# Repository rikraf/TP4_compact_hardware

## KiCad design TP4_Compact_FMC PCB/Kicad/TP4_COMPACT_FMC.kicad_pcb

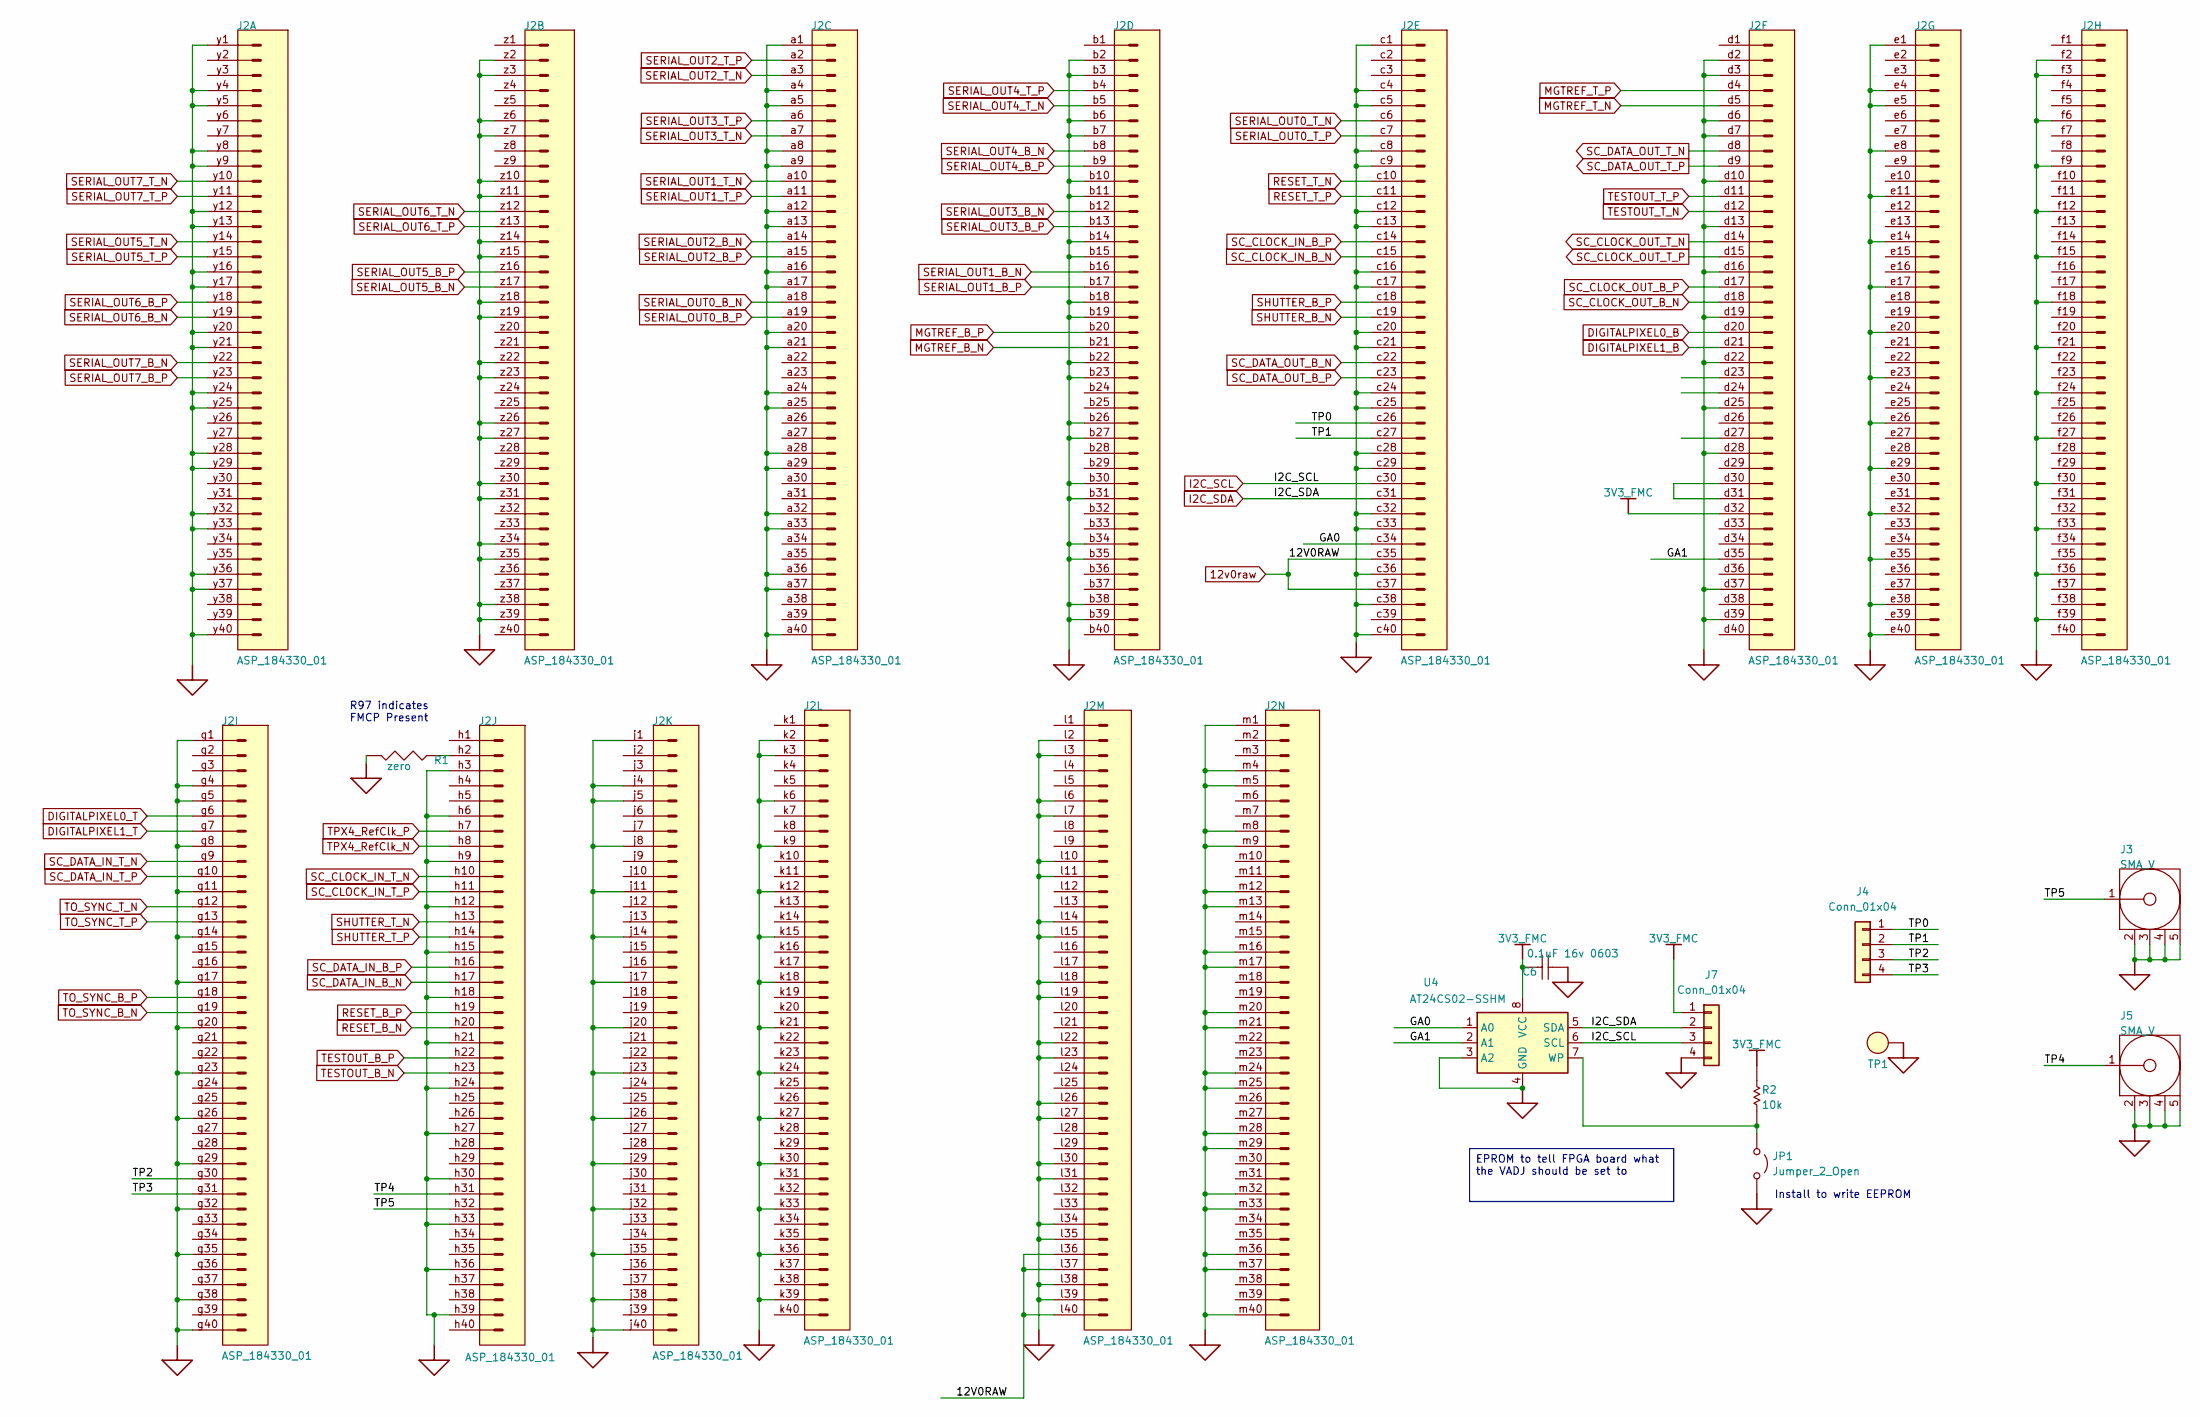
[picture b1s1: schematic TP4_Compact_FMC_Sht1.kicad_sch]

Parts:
C6: 0.1uF 0603; C_0603_1608Metric; MANUFACTURER_PART_NUMBER C0603C104K4RACTU
J2: ASP_184330_01; SAMTEC_ASP_184330_01; MANUFACTURER_PART_NUMBER ASP-184330-01
J3, J5: SMA_V; SMA_Amphenol_901-144_Vertical; MANUFACTURER_PART_NUMBER SMA-J-P-H-ST-MT1
J4, J7: Conn_01x04; PinHeader_1x04_P2.54mm_Vertical; MANUFACTURER_PART_NUMBER 61300411121
JP1: Jumper_2_Open; TestPoint_2Pads_Pitch2.54mm_Drill0.8mm; MANUFACTURER_PART_NUMBER 61300211121
R1: zero; R_0603_1608Metric; MANUFACTURER_PART_NUMBER RC0603JR-070RL
R2: 10k; R_0603_1608Metric; MANUFACTURER_PART_NUMBER CR0603-FX-1002ELF
TP1: through-hole pad; SolderWire-0.1sqmm_1x01_D0.4mm_OD1mm
U4: AT24CS02-SSHM; SOIC-8_3.9x4.9mm_P1.27mm; MANUFACTURER_PART_NUMBER AT24C02C-SSHM-T

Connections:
3V3_FMC: C6.2, J2.d32, J7.1, R2.2, U4.8 (VCC)
12v0raw: J2.c35, J2.c37, J2.l36, J2.l37, J2.l40; also elsewhere on the board
/FMC_osc/GA0: J2.c34, U4.1 (A0)
/FMC_osc/GA1: J2.d35, U4.2 (A1)
/FMC_osc/TP0: J2.c26, J4.1
/FMC_osc/TP1: J2.c27, J4.2
/FMC_osc/TP2: J2.g30, J4.3
/FMC_osc/TP3: J2.g31, J4.4
/FMC_osc/TP4: J2.h31, J5.1 (Signal)
/FMC_osc/TP5: J2.h32, J3.1 (Signal)
DIGITALPIXEL0_B: J2.d20; also elsewhere on the board
DIGITALPIXEL0_T: J2.g6; also elsewhere on the board
DIGITALPIXEL1_B: J2.d21; also elsewhere on the board
DIGITALPIXEL1_T: J2.g7; also elsewhere on the board
GND: C6.1, J2.a1, J2.a4, J2.a5, J2.a8, J2.a9, J2.a12, J2.a13, J2.a16, J2.a17, J2.a20, J2.a21, J2.a24, J2.a25, J2.a28, J2.a29, J2.a32, J2.a33, J2.a36, J2.a37, J2.a40, J2.b2, J2.b3, J2.b6, J2.b7, J2.b10, J2.b11, J2.b14, J2.b15, J2.b18, J2.b19, J2.b22, J2.b23, J2.b26, J2.b27, J2.b30, J2.b31, J2.b34, J2.b35, J2.b38, J2.b39, J2.c1, J2.c4, J2.c5, J2.c8, J2.c9, J2.c12, J2.c13, J2.c16, J2.c17, J2.c20, J2.c21, J2.c24, J2.c25, J2.c28, J2.c29, J2.c32, J2.c33, J2.c36, J2.c38, J2.c40, J2.d2, J2.d3, J2.d6, J2.d7, J2.d10, J2.d13, J2.d16, J2.d19, J2.d22, J2.d25, J2.d28, J2.d37, J2.d39, J2.e1, J2.e4, J2.e5, J2.e8, J2.e11, J2.e14, J2.e17, J2.e20, J2.e23, J2.e26, J2.e29, J2.e32, J2.e35, J2.e38, J2.e40, J2.f2, J2.f3, J2.f6, J2.f9, J2.f12, J2.f15, J2.f18, J2.f21, J2.f24, J2.f27, J2.f30, J2.f33, J2.f36, J2.f39, J2.g1, J2.g4, J2.g5, J2.g8, J2.g11, J2.g14, J2.g17, J2.g20, J2.g23, J2.g26, J2.g29, J2.g32, J2.g35, J2.g38, J2.g40, J2.h3, J2.h6, J2.h9, J2.h12, J2.h15, J2.h18, J2.h21, J2.h24, J2.h27, J2.h30, J2.h33, J2.h36, J2.h39, J2.j1, J2.j4, J2.j5, J2.j8, J2.j11, J2.j14, J2.j17, J2.j20, J2.j23, J2.j26, J2.j29, J2.j32, J2.j35, J2.j38, J2.j40, J2.k2, J2.k3, J2.k6, J2.k9, J2.k12, J2.k15, J2.k18, J2.k21, J2.k24, J2.k27, J2.k30, J2.k33, J2.k36, J2.k39, J2.l2, J2.l3, J2.l6, J2.l7, J2.l10, J2.l11, J2.l14, J2.l15, J2.l18, J2.l19, J2.l22, J2.l23, J2.l26, J2.l27, J2.l30, J2.l31, J2.l34, J2.l35, J2.l38, J2.l39, J2.m1, J2.m4, J2.m5, J2.m8, J2.m9, J2.m12, J2.m13, J2.m16, J2.m17, J2.m20, J2.m21, J2.m24, J2.m25, J2.m28, J2.m29, J2.m32, J2.m33, J2.m36, J2.m37, J2.m40, J2.y1, J2.y4, J2.y5, J2.y8, J2.y9, J2.y12, J2.y13, J2.y16, J2.y17, J2.y20, J2.y21, J2.y24, J2.y25, J2.y28, J2.y29, J2.y32, J2.y33, J2.y36, J2.y37, J2.y40, J2.z2, J2.z3, J2.z6, J2.z7, J2.z10, J2.z11, J2.z14, J2.z15, J2.z18, J2.z19, J2.z22, J2.z23, J2.z26, J2.z27, J2.z30, J2.z31, J2.z34, J2.z35, J2.z38, J2.z39, J3.2 (GND), J3.3 (GND), J3.4 (GND), J3.5 (GND), J5.2 (GND), J5.3 (GND), J5.4 (GND), J5.5 (GND), J7.4, JP1.2 (B), R1.2, TP1.1, U4.3 (A2), U4.4 (GND); also elsewhere on the board
I2C_SCL: J2.c30, J7.3, U4.6 (SCL); also elsewhere on the board
I2C_SDA: J2.c31, J7.2, U4.5 (SDA); also elsewhere on the board
MGTREF_B_N: J2.b21; also elsewhere on the board
MGTREF_B_P: J2.b20; also elsewhere on the board
MGTREF_T_N: J2.d5; also elsewhere on the board
MGTREF_T_P: J2.d4; also elsewhere on the board
unnamed: J2.d30, J2.d31
unnamed: J2.h2, R1.1
unnamed: JP1.1 (A), R2.1, U4.7 (WP)
RESET_B_N: J2.h20; also elsewhere on the board
RESET_B_P: J2.h19; also elsewhere on the board
RESET_T_N: J2.c10; also elsewhere on the board
RESET_T_P: J2.c11; also elsewhere on the board
SC_CLOCK_IN_B_N: J2.c15; also elsewhere on the board
SC_CLOCK_IN_B_P: J2.c14; also elsewhere on the board
SC_CLOCK_IN_T_N: J2.h10; also elsewhere on the board
SC_CLOCK_IN_T_P: J2.h11; also elsewhere on the board
SC_CLOCK_OUT_B_N: J2.d18; also elsewhere on the board
SC_CLOCK_OUT_B_P: J2.d17; also elsewhere on the board
SC_CLOCK_OUT_T_N: J2.d14; also elsewhere on the board
SC_CLOCK_OUT_T_P: J2.d15; also elsewhere on the board
SC_DATA_IN_B_N: J2.h17; also elsewhere on the board
SC_DATA_IN_B_P: J2.h16; also elsewhere on the board
SC_DATA_IN_T_N: J2.g9; also elsewhere on the board
SC_DATA_IN_T_P: J2.g10; also elsewhere on the board
SC_DATA_OUT_B_N: J2.c22; also elsewhere on the board
SC_DATA_OUT_B_P: J2.c23; also elsewhere on the board
SC_DATA_OUT_T_N: J2.d8; also elsewhere on the board
SC_DATA_OUT_T_P: J2.d9; also elsewhere on the board
SERIAL_OUT0_B_N: J2.a18; also elsewhere on the board
SERIAL_OUT0_B_P: J2.a19; also elsewhere on the board
SERIAL_OUT0_T_N: J2.c6; also elsewhere on the board
SERIAL_OUT0_T_P: J2.c7; also elsewhere on the board
SERIAL_OUT1_B_N: J2.b16; also elsewhere on the board
SERIAL_OUT1_B_P: J2.b17; also elsewhere on the board
SERIAL_OUT1_T_N: J2.a10; also elsewhere on the board
SERIAL_OUT1_T_P: J2.a11; also elsewhere on the board
SERIAL_OUT2_B_N: J2.a14; also elsewhere on the board
SERIAL_OUT2_B_P: J2.a15; also elsewhere on the board
SERIAL_OUT2_T_N: J2.a3; also elsewhere on the board
SERIAL_OUT2_T_P: J2.a2; also elsewhere on the board
SERIAL_OUT3_B_N: J2.b12; also elsewhere on the board
SERIAL_OUT3_B_P: J2.b13; also elsewhere on the board
SERIAL_OUT3_T_N: J2.a7; also elsewhere on the board
SERIAL_OUT3_T_P: J2.a6; also elsewhere on the board
SERIAL_OUT4_B_N: J2.b8; also elsewhere on the board
SERIAL_OUT4_B_P: J2.b9; also elsewhere on the board
SERIAL_OUT4_T_N: J2.b5; also elsewhere on the board
SERIAL_OUT4_T_P: J2.b4; also elsewhere on the board
SERIAL_OUT5_B_N: J2.z17; also elsewhere on the board
SERIAL_OUT5_B_P: J2.z16; also elsewhere on the board
SERIAL_OUT5_T_N: J2.y14; also elsewhere on the board
SERIAL_OUT5_T_P: J2.y15; also elsewhere on the board
SERIAL_OUT6_B_N: J2.y19; also elsewhere on the board
SERIAL_OUT6_B_P: J2.y18; also elsewhere on the board
SERIAL_OUT6_T_N: J2.z12; also elsewhere on the board
SERIAL_OUT6_T_P: J2.z13; also elsewhere on the board
SERIAL_OUT7_B_N: J2.y22; also elsewhere on the board
SERIAL_OUT7_B_P: J2.y23; also elsewhere on the board
SERIAL_OUT7_T_N: J2.y10; also elsewhere on the board
SERIAL_OUT7_T_P: J2.y11; also elsewhere on the board
SHUTTER_B_N: J2.c19; also elsewhere on the board
SHUTTER_B_P: J2.c18; also elsewhere on the board
SHUTTER_T_N: J2.h13; also elsewhere on the board
SHUTTER_T_P: J2.h14; also elsewhere on the board
TESTOUT_B_N: J2.h23; also elsewhere on the board
TESTOUT_B_P: J2.h22; also elsewhere on the board
TESTOUT_T_N: J2.d12; also elsewhere on the board
TESTOUT_T_P: J2.d11; also elsewhere on the board
TO_SYNC_B_N: J2.g19; also elsewhere on the board
TO_SYNC_B_P: J2.g18; also elsewhere on the board
TO_SYNC_T_N: J2.g12; also elsewhere on the board
TO_SYNC_T_P: J2.g13; also elsewhere on the board
TPX4_RefClk_N: J2.h8; also elsewhere on the board
TPX4_RefClk_P: J2.h7; also elsewhere on the board

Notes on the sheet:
Install to write EEPROM
R97 indicates FMCP Present
EPROM to tell FPGA board what the VADJ should be set to

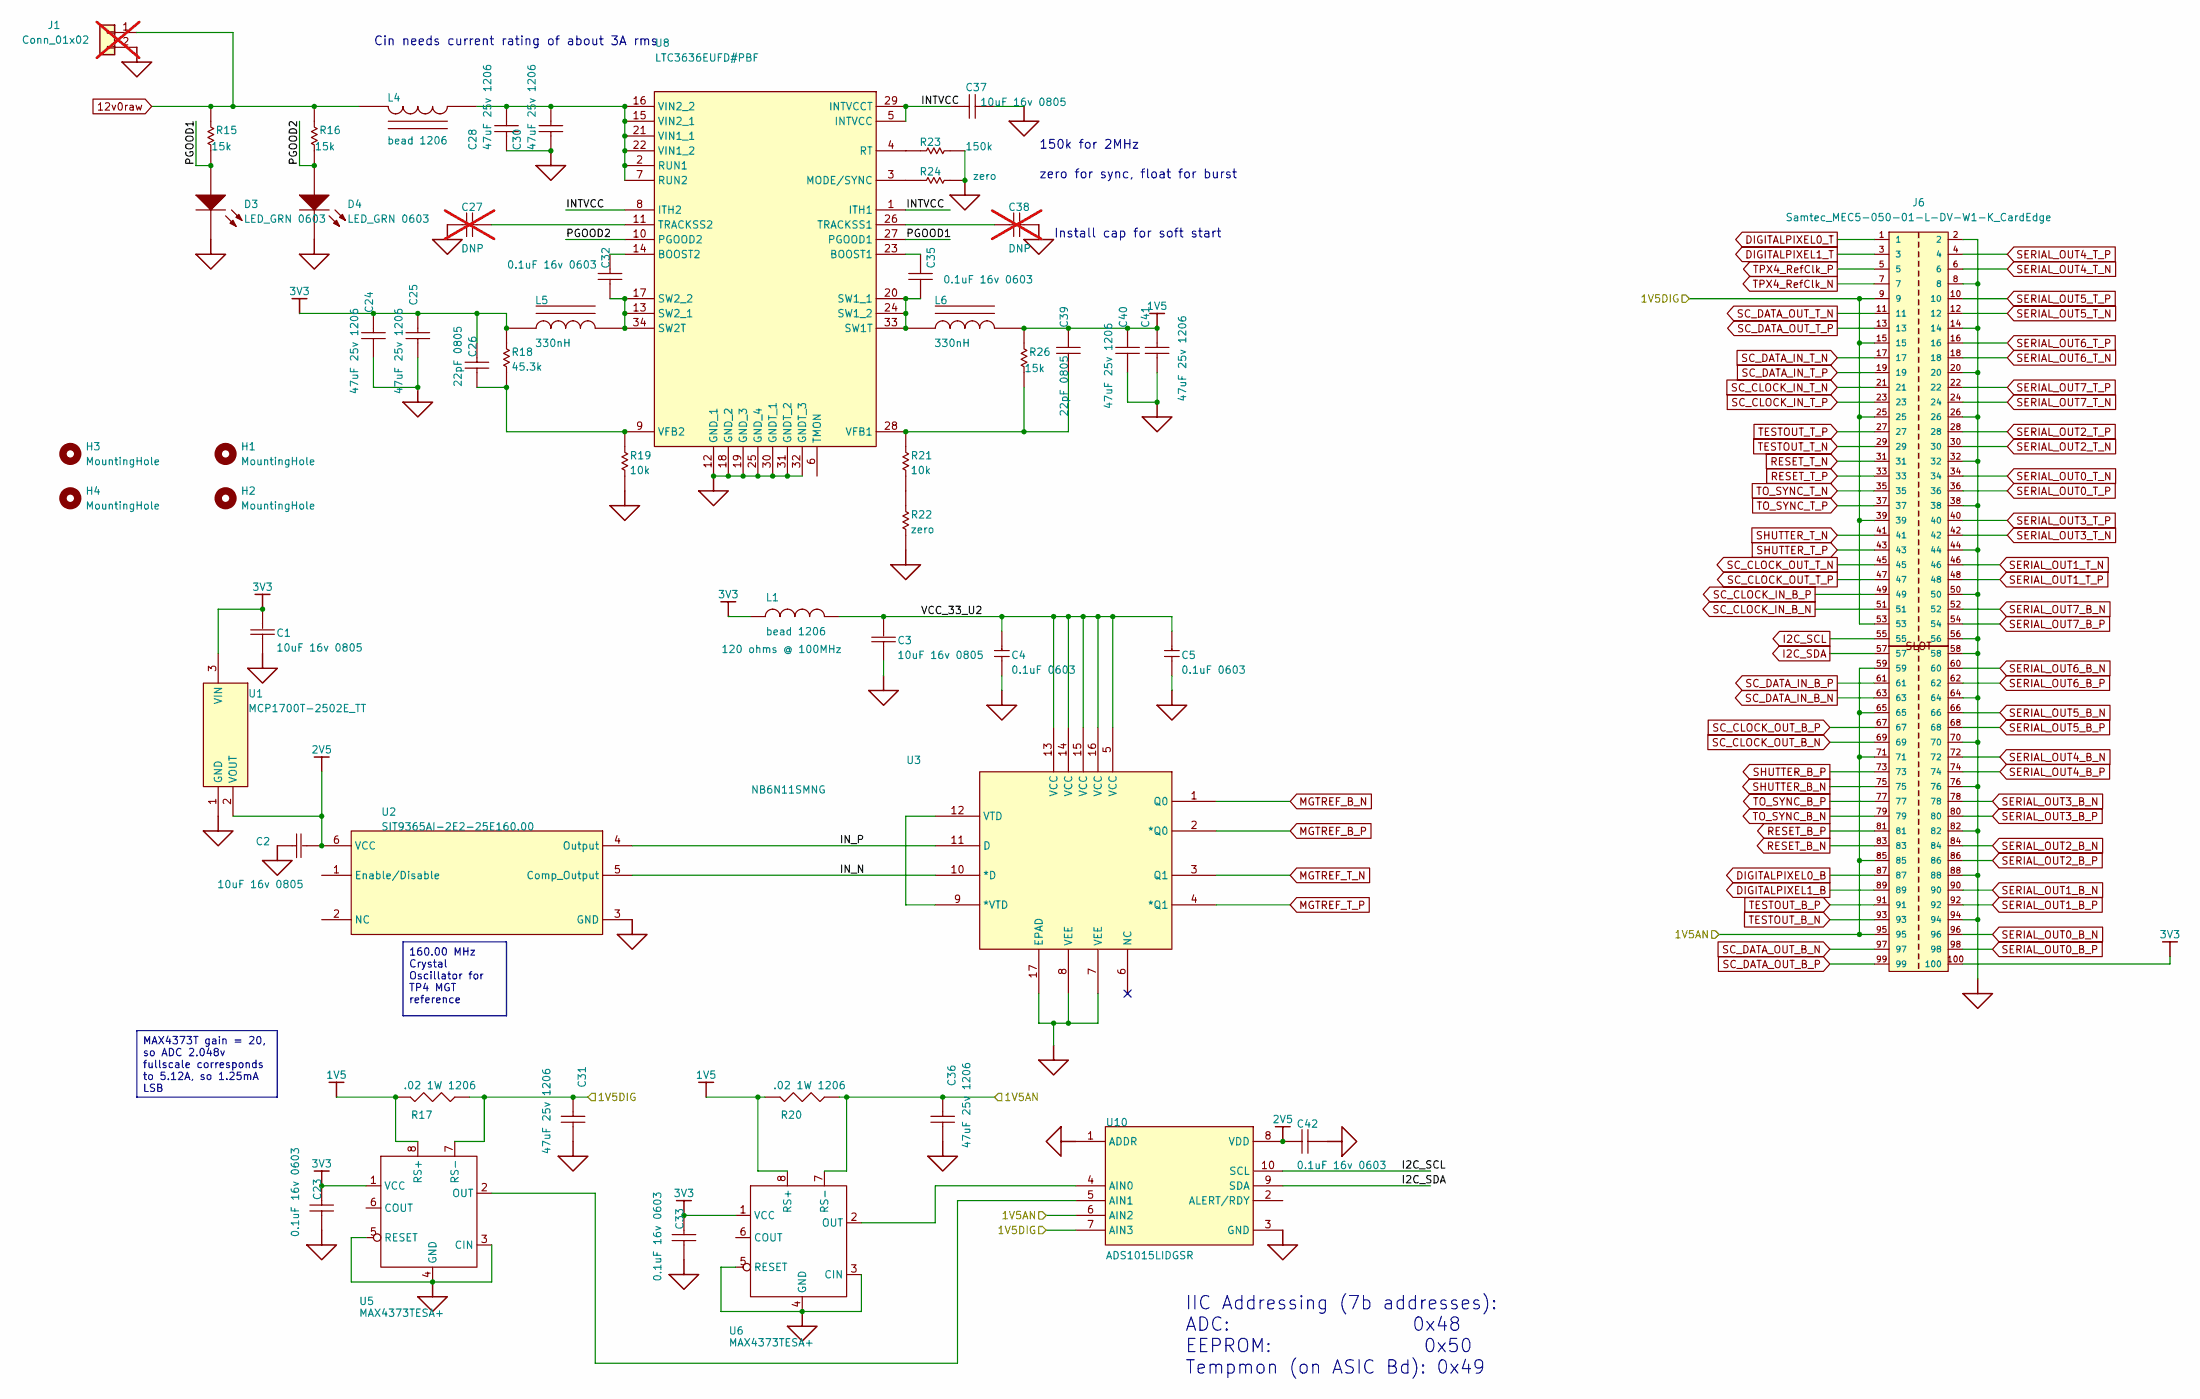
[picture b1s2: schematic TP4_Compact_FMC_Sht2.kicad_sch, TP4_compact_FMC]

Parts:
C1, C2, C3, C37: 10uF 16v 0805; C_0805_2012Metric; MANUFACTURER_PART_NUMBER CL21B106KOQNNNE
C4, C5: 0.1uF 0603; C_0603_1608Metric; VOLTAGE - RATED 6.3V; TOLERANCE ±10%; MANUFACTURER_PART_NUMBER C0603C104K4RACTU
C23, C32, C33, C35, C42: 0.1uF 0603; C_0603_1608Metric; MANUFACTURER_PART_NUMBER C0603C104K4RACTU
C24, C25, C28, C30, C31, C36, C40, C41: 47uF 25v 1206; C_1206_3216Metric; MANUFACTURER_PART_NUMBER GMC31X5R476M25NT
C26, C39: 22pF 0603; C_0603_1608Metric; MANUFACTURER_PART_NUMBER C0603C220J5GACTU
C27, C38: DNP; C_0603_1608Metric; not fitted
D3, D4: LED_GRN 0603; LED_0603_1608Metric; MANUFACTURER_PART_NUMBER LTST-C190GKT
H1, H2, H3, H4: MountingHole; MountingHole_3.2mm_M3
J1: Conn_01x02; Molex_SL_171971-0002_1x02_P2.54mm_Vertical; not fitted
J6: Samtec_MEC5-050-01-L-DV-W1-K_CardEdge; MPN MEC5-050-01-L-DV-W1-K-TR
L1: bead 1206; L_1206_3216Metric; CURRENT RATING 4 Amps; MANUFACTURER PART NUMBER HI1206P121R-10
L4: bead 1206; L_1206_3216Metric; MANUFACTURER_PART_NUMBER HI1206T500R-10
L5, L6: 330nH; L_Wuerth_HCI-5040; MANUFACTURER_PART_NUMBER 744316033
R15, R16, R26: 15k; R_0603_1608Metric; MANUFACTURER_PART_NUMBER CR0603-FX-1502ELF
R17, R20: .02 1W 1206; R_1206_3216Metric; MANUFACTURER_PART_NUMBER LVT12R0200FER
R18: 45.3k; R_0603_1608Metric; MANUFACTURER_PART_NUMBER CR0603-FX-4532ELF
R19, R21: 10k; R_0603_1608Metric; MANUFACTURER_PART_NUMBER CR0603-FX-1002ELF
R22, R24: zero; R_0603_1608Metric; MANUFACTURER_PART_NUMBER RC0603JR-070RL
R23: 150k; R_0603_1608Metric; MANUFACTURER_PART_NUMBER CR0603-FX-1503ELF
U1: MCP1700T-2502E_TT; SOT-23-3; MANUFACTURER_PART_NUMBER MCP1700T-2502E/TT; MOUSER PART NUMBER 579-MCP1700T2502E/TT
U2: SIT9365AI-2E2-25E160.00; Oscillator_SMD_IDT_JU6-6_7.0x5.0mm_P2.54mm; MANUFACTURER_PART_NUMBER SIT9365AI-2E2-25E160.000000
U3: NB6N11SMNG; QFN-16-1EP_3x3mm_P0.5mm_EP1.7x1.7mm_ThermalVias; MANUFACTURER_PART_NUMBER NB6N11SMNG
U5, U6: MAX4373TESA+; SO-8_3.9x4.9mm_P1.27mm; MANUFACTURER_PART_NUMBER MAX4373TESA+T
U8: LTC3636EUFD#PBF; LTC3636EUFDPBF; MANUFACTURER_PART_NUMBER LTC3636EUFD#PBF; MOUSER PART NUMBER 584-LTC3636EUFDPBF
U10: ADS1015LIDGSR; SOP50P490X110-10N; MANUFACTURER_PART_NUMBER ADS1015LIDGSR; MOUSER PART NUMBER 595-ADS1015LIDGSR

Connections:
1V5: C39.2, C40.2, C41.2, L6.2, R17.2, R20.2, R26.2, U5.8 (RS+), U6.8 (RS+)
2V5: C2.1, C42.2, U1.2 (VOUT), U2.6 (VCC), U10.8 (VDD)
3V3: C1.1, C23.2, C24.2, C25.2, C26.2, C33.2, J6.100, L1.1, L5.1, R18.2, U1.3 (VIN), U5.1 (VCC), U6.1 (VCC)
12v0raw: J1.1, L4.2, R15.2, R16.2; also elsewhere on the board
/MEC4_power/1V5AN: C36.2, J6.59, J6.65, J6.71, J6.85, J6.95, R20.1, U6.7 (RS-), U10.6 (AIN2)
/MEC4_power/1V5DIG: C31.2, J6.9, J6.15, J6.25, J6.39, J6.53, R17.1, U5.7 (RS-), U10.7 (AIN3)
/MEC4_power/INTVCC: C37.2, U8.1 (ITH1), U8.5 (INTVCC), U8.8 (ITH2), U8.29 (INTVCCT)
/MEC4_power/IN_N: U2.5 (Comp_Output), U3.10 (*D)
/MEC4_power/IN_P: U2.4 (Output), U3.11 (D)
/MEC4_power/PGOOD1: D3.1 (A), R15.1, U8.27 (PGOOD1)
/MEC4_power/PGOOD2: D4.1 (A), R16.1, U8.10 (PGOOD2)
/MEC4_power/VCC_33_U2: C3.1, C4.1, C5.1, L1.2, U3.5 (VCC), U3.13 (VCC), U3.14 (VCC), U3.15 (VCC), U3.16 (VCC)
DIGITALPIXEL0_B: J6.87; also elsewhere on the board
DIGITALPIXEL0_T: J6.1; also elsewhere on the board
DIGITALPIXEL1_B: J6.89; also elsewhere on the board
DIGITALPIXEL1_T: J6.3; also elsewhere on the board
GND: C1.2, C2.2, C3.2, C4.2, C5.2, C23.1, C24.1, C25.1, C27.2, C28.1, C30.1, C31.1, C33.1, C36.1, C37.1, C38.1, C40.1, C41.1, C42.1, D3.2 (K), D4.2 (K), J1.2, J6.2, J6.8, J6.14, J6.20, J6.26, J6.32, J6.38, J6.44, J6.50, J6.56, J6.58, J6.64, J6.70, J6.76, J6.82, J6.88, J6.94, R19.1, R22.1, R23.1, R24.1, U1.1 (GND), U2.3 (GND), U3.7 (VEE), U3.8 (VEE), U3.17 (EPAD), U5.3 (CIN), U5.4 (GND), U5.5 (RESET), U6.3 (CIN), U6.4 (GND), U6.5 (RESET), U8.12 (GND_1), U8.18 (GND_2), U8.19 (GND_3), U8.25 (GND_4), U8.30 (GNDT_1), U8.31 (GNDT_2), U8.32 (GNDT_3), U10.1 (ADDR), U10.3 (GND); also elsewhere on the board
I2C_SCL: J6.55, U10.10 (SCL); also elsewhere on the board
I2C_SDA: J6.57, U10.9 (SDA); also elsewhere on the board
MGTREF_B_N: U3.1 (Q0); also elsewhere on the board
MGTREF_B_P: U3.2 (*Q0); also elsewhere on the board
MGTREF_T_N: U3.3 (Q1); also elsewhere on the board
MGTREF_T_P: U3.4 (*Q1); also elsewhere on the board
unnamed: R21.1, R22.2
unnamed: U3.9 (*VTD), U3.12 (VTD)
unnamed: C35.2, U8.23 (BOOST1)
unnamed: C32.2, U8.14 (BOOST2)
unnamed: R24.2, U8.3 (MODE/SYNC)
unnamed: R23.2, U8.4 (RT)
unnamed: C28.2, C30.2, L4.1, U8.2 (RUN1), U8.7 (RUN2), U8.15 (VIN2_1), U8.16 (VIN2_2), U8.21 (VIN1_1), U8.22 (VIN1_2)
unnamed: C35.1, L6.1, U8.20 (SW1_1), U8.24 (SW1_2), U8.33 (SW1T)
unnamed: C32.1, L5.2, U8.13 (SW2_1), U8.17 (SW2_2), U8.34 (SW2T)
unnamed: C38.2, U8.26 (TRACKSS1)
unnamed: C27.1, U8.11 (TRACKSS2)
unnamed: C39.1, R21.2, R26.1, U8.28 (VFB1)
unnamed: C26.1, R18.1, R19.2, U8.9 (VFB2)
unnamed: U6.2 (OUT), U10.4 (AIN0)
unnamed: U5.2 (OUT), U10.5 (AIN1)
RESET_B_N: J6.83; also elsewhere on the board
RESET_B_P: J6.81; also elsewhere on the board
RESET_T_N: J6.31; also elsewhere on the board
RESET_T_P: J6.33; also elsewhere on the board
SC_CLOCK_IN_B_N: J6.51; also elsewhere on the board
SC_CLOCK_IN_B_P: J6.49; also elsewhere on the board
SC_CLOCK_IN_T_N: J6.21; also elsewhere on the board
SC_CLOCK_IN_T_P: J6.23; also elsewhere on the board
SC_CLOCK_OUT_B_N: J6.69; also elsewhere on the board
SC_CLOCK_OUT_B_P: J6.67; also elsewhere on the board
SC_CLOCK_OUT_T_N: J6.45; also elsewhere on the board
SC_CLOCK_OUT_T_P: J6.47; also elsewhere on the board
SC_DATA_IN_B_N: J6.63; also elsewhere on the board
SC_DATA_IN_B_P: J6.61; also elsewhere on the board
SC_DATA_IN_T_N: J6.17; also elsewhere on the board
SC_DATA_IN_T_P: J6.19; also elsewhere on the board
SC_DATA_OUT_B_N: J6.97; also elsewhere on the board
SC_DATA_OUT_B_P: J6.99; also elsewhere on the board
SC_DATA_OUT_T_N: J6.11; also elsewhere on the board
SC_DATA_OUT_T_P: J6.13; also elsewhere on the board
SERIAL_OUT0_B_N: J6.96; also elsewhere on the board
SERIAL_OUT0_B_P: J6.98; also elsewhere on the board
SERIAL_OUT0_T_N: J6.34; also elsewhere on the board
SERIAL_OUT0_T_P: J6.36; also elsewhere on the board
SERIAL_OUT1_B_N: J6.90; also elsewhere on the board
SERIAL_OUT1_B_P: J6.92; also elsewhere on the board
SERIAL_OUT1_T_N: J6.46; also elsewhere on the board
SERIAL_OUT1_T_P: J6.48; also elsewhere on the board
SERIAL_OUT2_B_N: J6.84; also elsewhere on the board
SERIAL_OUT2_B_P: J6.86; also elsewhere on the board
SERIAL_OUT2_T_N: J6.30; also elsewhere on the board
SERIAL_OUT2_T_P: J6.28; also elsewhere on the board
SERIAL_OUT3_B_N: J6.78; also elsewhere on the board
SERIAL_OUT3_B_P: J6.80; also elsewhere on the board
SERIAL_OUT3_T_N: J6.42; also elsewhere on the board
SERIAL_OUT3_T_P: J6.40; also elsewhere on the board
SERIAL_OUT4_B_N: J6.72; also elsewhere on the board
SERIAL_OUT4_B_P: J6.74; also elsewhere on the board
SERIAL_OUT4_T_N: J6.6; also elsewhere on the board
SERIAL_OUT4_T_P: J6.4; also elsewhere on the board
SERIAL_OUT5_B_N: J6.66; also elsewhere on the board
SERIAL_OUT5_B_P: J6.68; also elsewhere on the board
SERIAL_OUT5_T_N: J6.12; also elsewhere on the board
SERIAL_OUT5_T_P: J6.10; also elsewhere on the board
SERIAL_OUT6_B_N: J6.60; also elsewhere on the board
SERIAL_OUT6_B_P: J6.62; also elsewhere on the board
SERIAL_OUT6_T_N: J6.18; also elsewhere on the board
SERIAL_OUT6_T_P: J6.16; also elsewhere on the board
SERIAL_OUT7_B_N: J6.52; also elsewhere on the board
SERIAL_OUT7_B_P: J6.54; also elsewhere on the board
SERIAL_OUT7_T_N: J6.24; also elsewhere on the board
SERIAL_OUT7_T_P: J6.22; also elsewhere on the board
SHUTTER_B_N: J6.75; also elsewhere on the board
SHUTTER_B_P: J6.73; also elsewhere on the board
SHUTTER_T_N: J6.41; also elsewhere on the board
SHUTTER_T_P: J6.43; also elsewhere on the board
TESTOUT_B_N: J6.93; also elsewhere on the board
TESTOUT_B_P: J6.91; also elsewhere on the board
TESTOUT_T_N: J6.29; also elsewhere on the board
TESTOUT_T_P: J6.27; also elsewhere on the board
TO_SYNC_B_N: J6.79; also elsewhere on the board
TO_SYNC_B_P: J6.77; also elsewhere on the board
TO_SYNC_T_N: J6.35; also elsewhere on the board
TO_SYNC_T_P: J6.37; also elsewhere on the board
TPX4_RefClk_N: J6.7; also elsewhere on the board
TPX4_RefClk_P: J6.5; also elsewhere on the board

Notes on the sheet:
Install cap for soft start
150k for 2MHz
Cin needs current rating of about 3A rms
zero for sync, float for burst
MAX4373T gain = 20, so ADC 2.048v fullscale corresponds to 5.12A, so 1.25mA LSB
160.00 MHz Crystal Oscillator for TP4 MGT reference
IIC Addressing (7b addresses): ADC: 0x48 EEPROM: 0x50 Tempmon (on ASIC Bd): 0x49

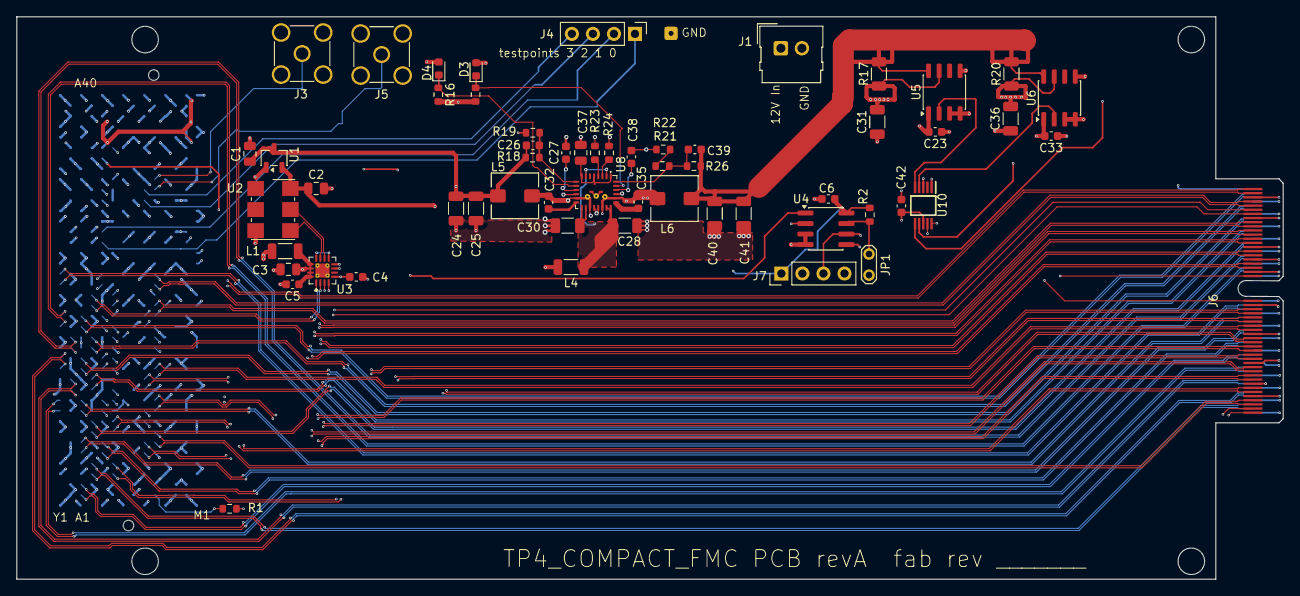
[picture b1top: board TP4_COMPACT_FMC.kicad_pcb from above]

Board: 6 copper layers, 152.9 x 67.9 mm, 64 parts (1 on the bottom side), 116 nets.

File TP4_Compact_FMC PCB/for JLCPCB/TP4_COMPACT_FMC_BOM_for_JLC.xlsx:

Comment | Designator | Footprint | MANUFACTURER_NAME | Value | ORDERNO | LCSC Part#
CL21B106KOQNNNE | C1,C2,C3,C37 | Capacitor_SMD:C_0805_2012Metric | Samsung Electromechanics | 10uF 16v 0805 | 1276-2872-1-ND
C0603C104K4RACTU | C4,C5,C6,C23,C32,C33,C35,C42 | Capacitor_SMD:C_0603_1608Metric | Kemet | 0.1uF 0603 | 399-C0603C104K4RACTUCT-ND
GMC31X5R476M25NT | C24,C25,C28,C30,C31,C36,C40,C41 | Capacitor_SMD:C_1206_3216Metric | TDK | 47uF 25v 1206 | 4713-GMC31X5R476M25NTCT-ND
C0603C220J5GACTU | C26,C39 | Capacitor_SMD:C_0603_1608Metric | Kemet | 22pF 0603 | 399-C0603C220J5GACTUCT-ND
LTST-C190GKT | D3,D4 | LED_SMD:LED_0603_1608Metric | Lite On | LED_GRN 0603 | 160-LTST-C190GKTCT-ND
ASP-184330-01 | J2 | Kicad RR Libs:SAMTEC_ASP_184330_01 | Samtec | ASP_184330_01 | SAM9173-ND
SMA-J-P-H-ST-MT1 | J3,J5 | Connector_Coaxial:SMA_Amphenol_901-144_Vertical | Samtec | SMA_V | SAM10718-ND
61300211121 | JP1 | TestPoint:TestPoint_2Pads_Pitch2.54mm_Drill0.8mm | Wurth | Jumper_2_Open | 732-5315-ND
HI1206T500R-10 | L1,L4 | Inductor_SMD:L_1206_3216Metric | Laird | bead 1206 | 240-2410-1-ND
744316033 | L5,L6 | Inductor_SMD:L_Wuerth_HCI-5040 | Wurth | 330nH | 732-6173-1-ND
RC0603JR-070RL | R1,R22,R24 | Resistor_SMD:R_0603_1608Metric | Yageo | zero | 311-0.0GRCT-ND
CR0603-FX-1002ELF | R2,R19,R21 | Resistor_SMD:R_0603_1608Metric | Bourns | 10k | CR0603-FX-1002ELFCT-ND
CR0603-FX-1502ELF | R15,R16,R26 | Resistor_SMD:R_0603_1608Metric | Bourns | 15k | CR0603-FX-1502ELFCT-ND
LVT12R0200FER | R17,R20 | Resistor_SMD:R_1206_3216Metric | Ohmite | .02 1W 1206 | 273-LVT12R0200FERCT-ND
CR0603-FX-4532ELF | R18 | Resistor_SMD:R_0603_1608Metric | Bourns | 45.3k | CR0603-FX-4532ELFCT-ND
CR0603-FX-1503ELF | R23 | Resistor_SMD:R_0603_1608Metric | Bourns | 150k | CR0603-FX-1503ELFCT-ND
MCP1700T-2502E/TT | U1 | Package_TO_SOT_SMD:SOT-23-3 | Microchip | MCP1700T-2502E_TT | MCP1700T-2502E/TTCT-ND
SIT9365AI-2E2-25E160.000000 | U2 | Oscillator:Oscillator_SMD_IDT_JU6-6_7.0x5.0mm_P2.54mm | SiTime | SIT9365AI-2E2-25E160.00 | 1473-SIT9365AI-2E2-25E160.000000-ND
NB6N11SMNG | U3 | Package_DFN_QFN:QFN-16-1EP_3x3mm_P0.5mm_EP1.7x1.7mm_ThermalVias | OnSemi | NB6N11SMNG | NB6N11SMNGOS-ND
AT24C02C-SSHM-T | U4 | Package_SO:SOIC-8_3.9x4.9mm_P1.27mm | Microchip | AT24CS02-SSHM | AT24C02C-SSHM-TCT-ND
LTC3636EUFD#PBF | U8 | TP4_FMC:LTC3636EUFDPBF | Analog Devices | LTC3636EUFD#PBF | 505-LTC3636EUFD#PBF-ND
ADS1015LIDGSR | U10 | TP4_FMC:SOP50P490X110-10N | Texas Instruments | ADS1015LIDGSR | 296-ADS1015LIDGSRCT-ND

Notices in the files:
parts and their libraries:
COPYRIGHT: Copyright (C) 2018 Accelerated Designs. All rights reserved
COPYRIGHT: Copyright (C) 2016 Accelerated Designs. All rights reserved
